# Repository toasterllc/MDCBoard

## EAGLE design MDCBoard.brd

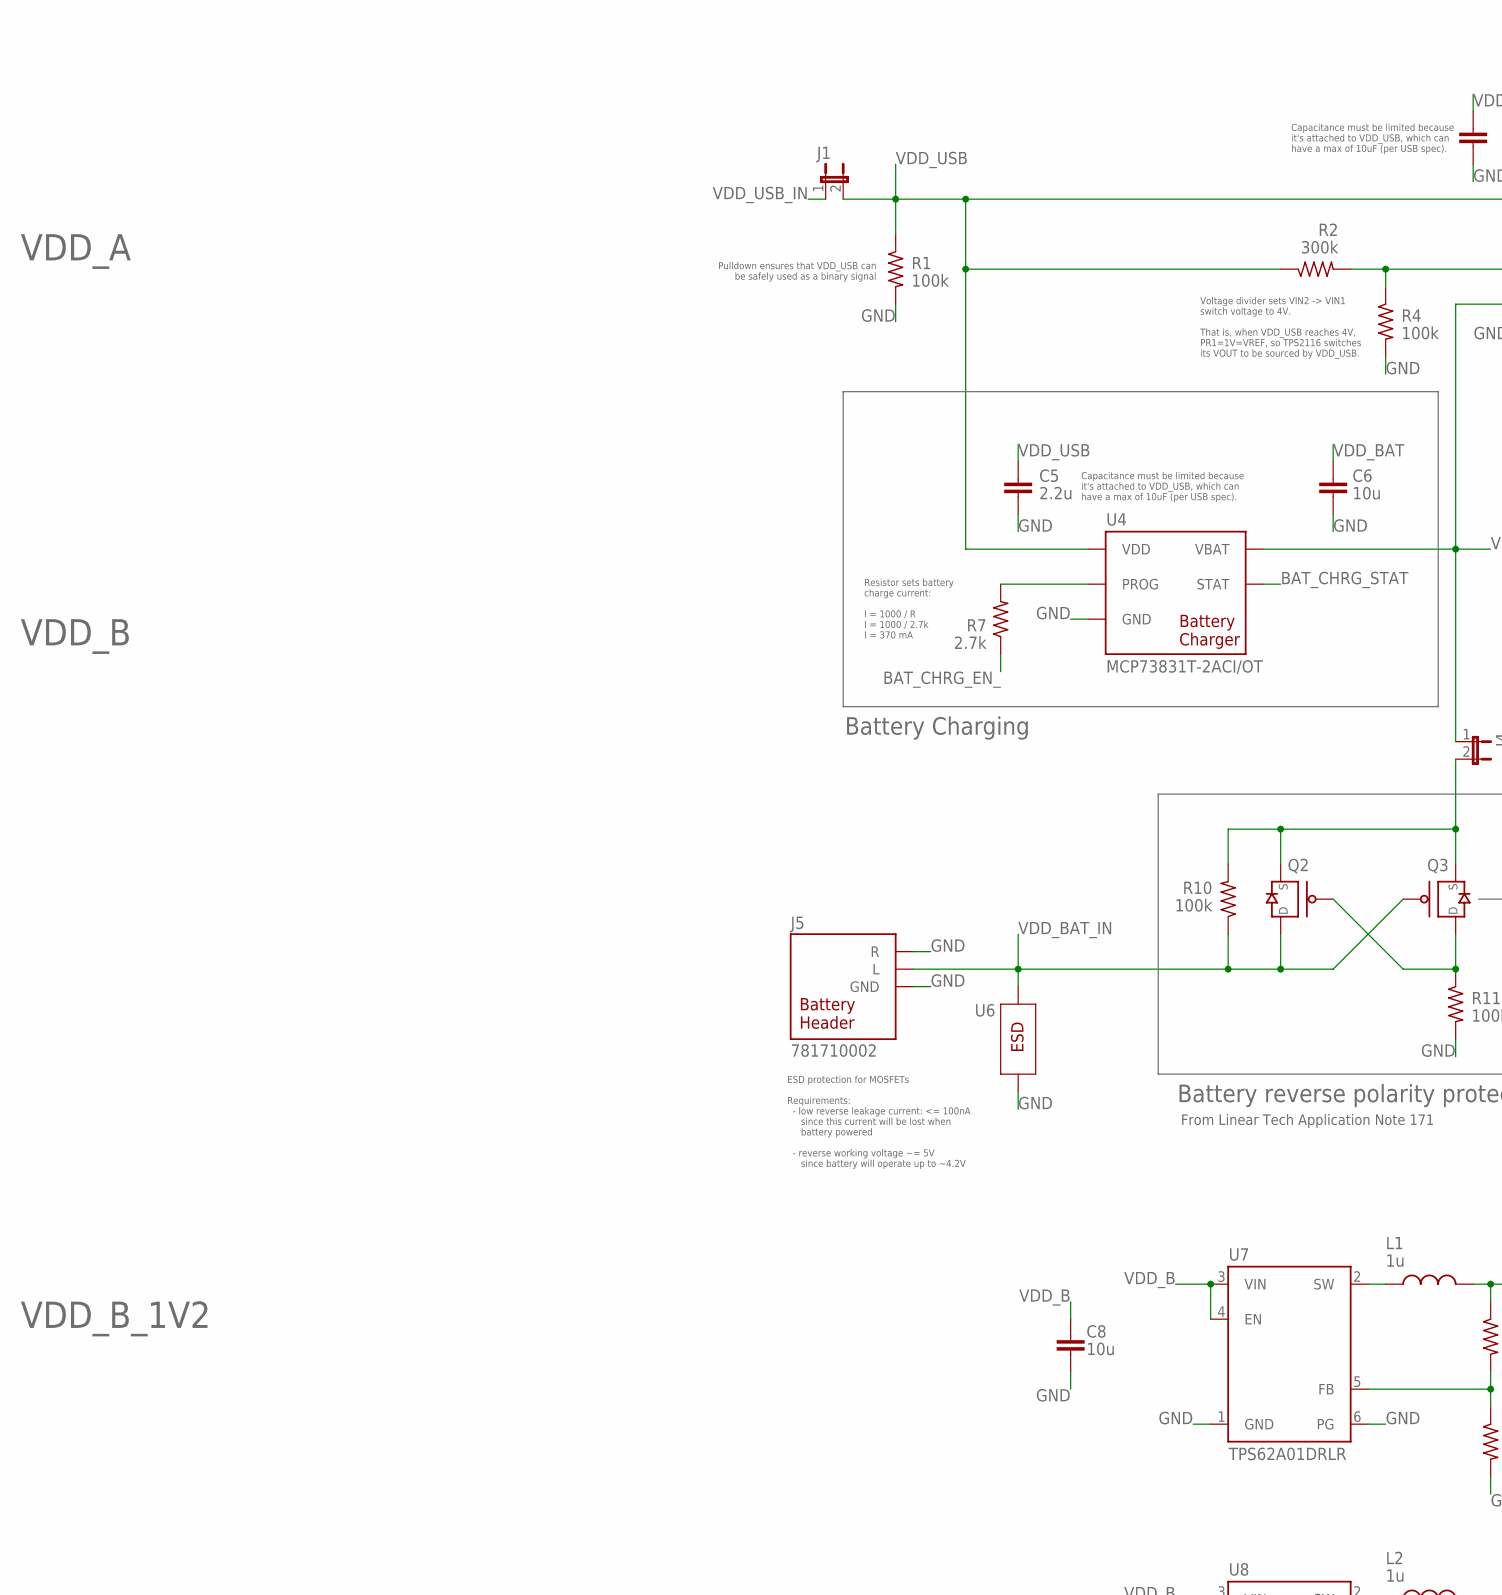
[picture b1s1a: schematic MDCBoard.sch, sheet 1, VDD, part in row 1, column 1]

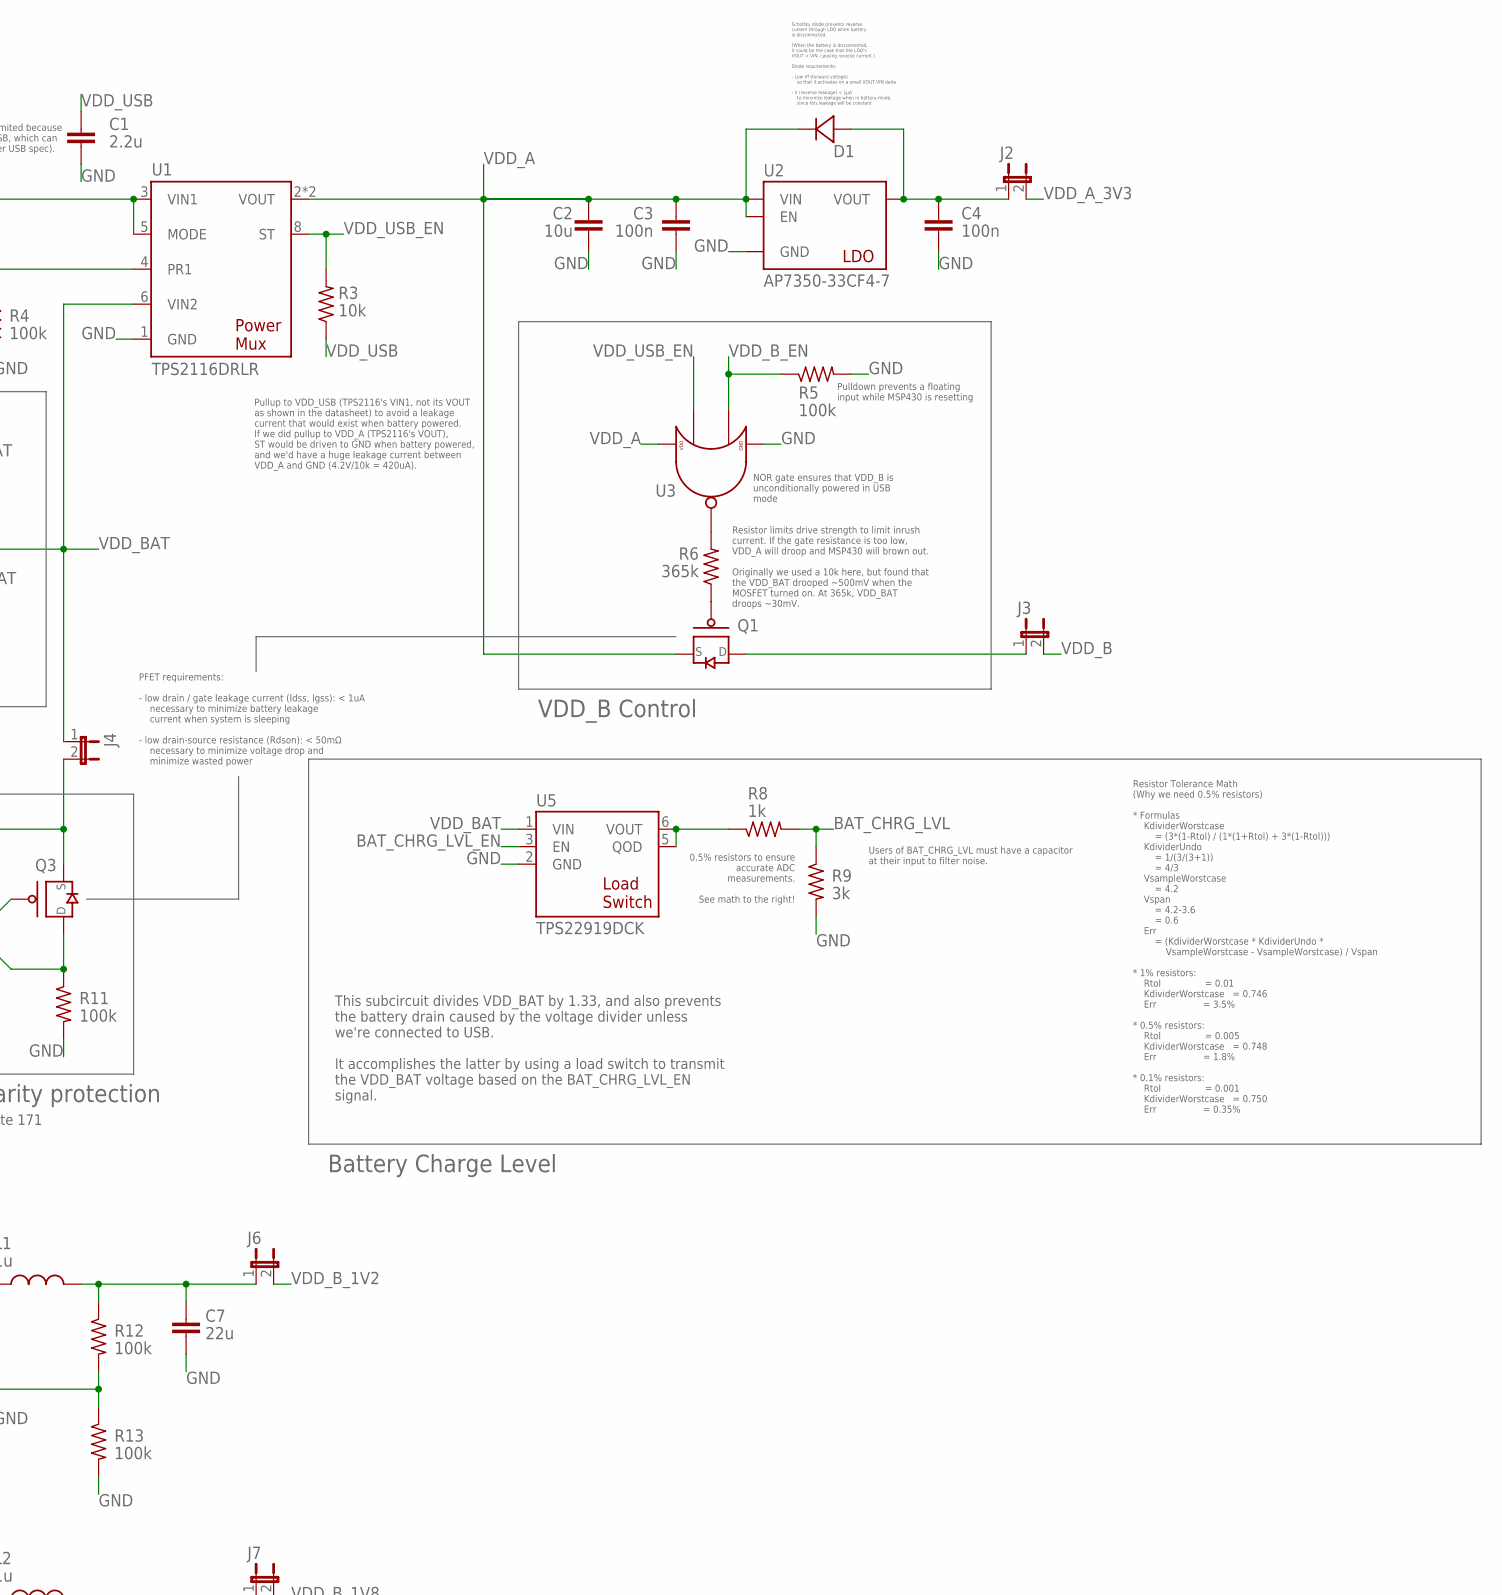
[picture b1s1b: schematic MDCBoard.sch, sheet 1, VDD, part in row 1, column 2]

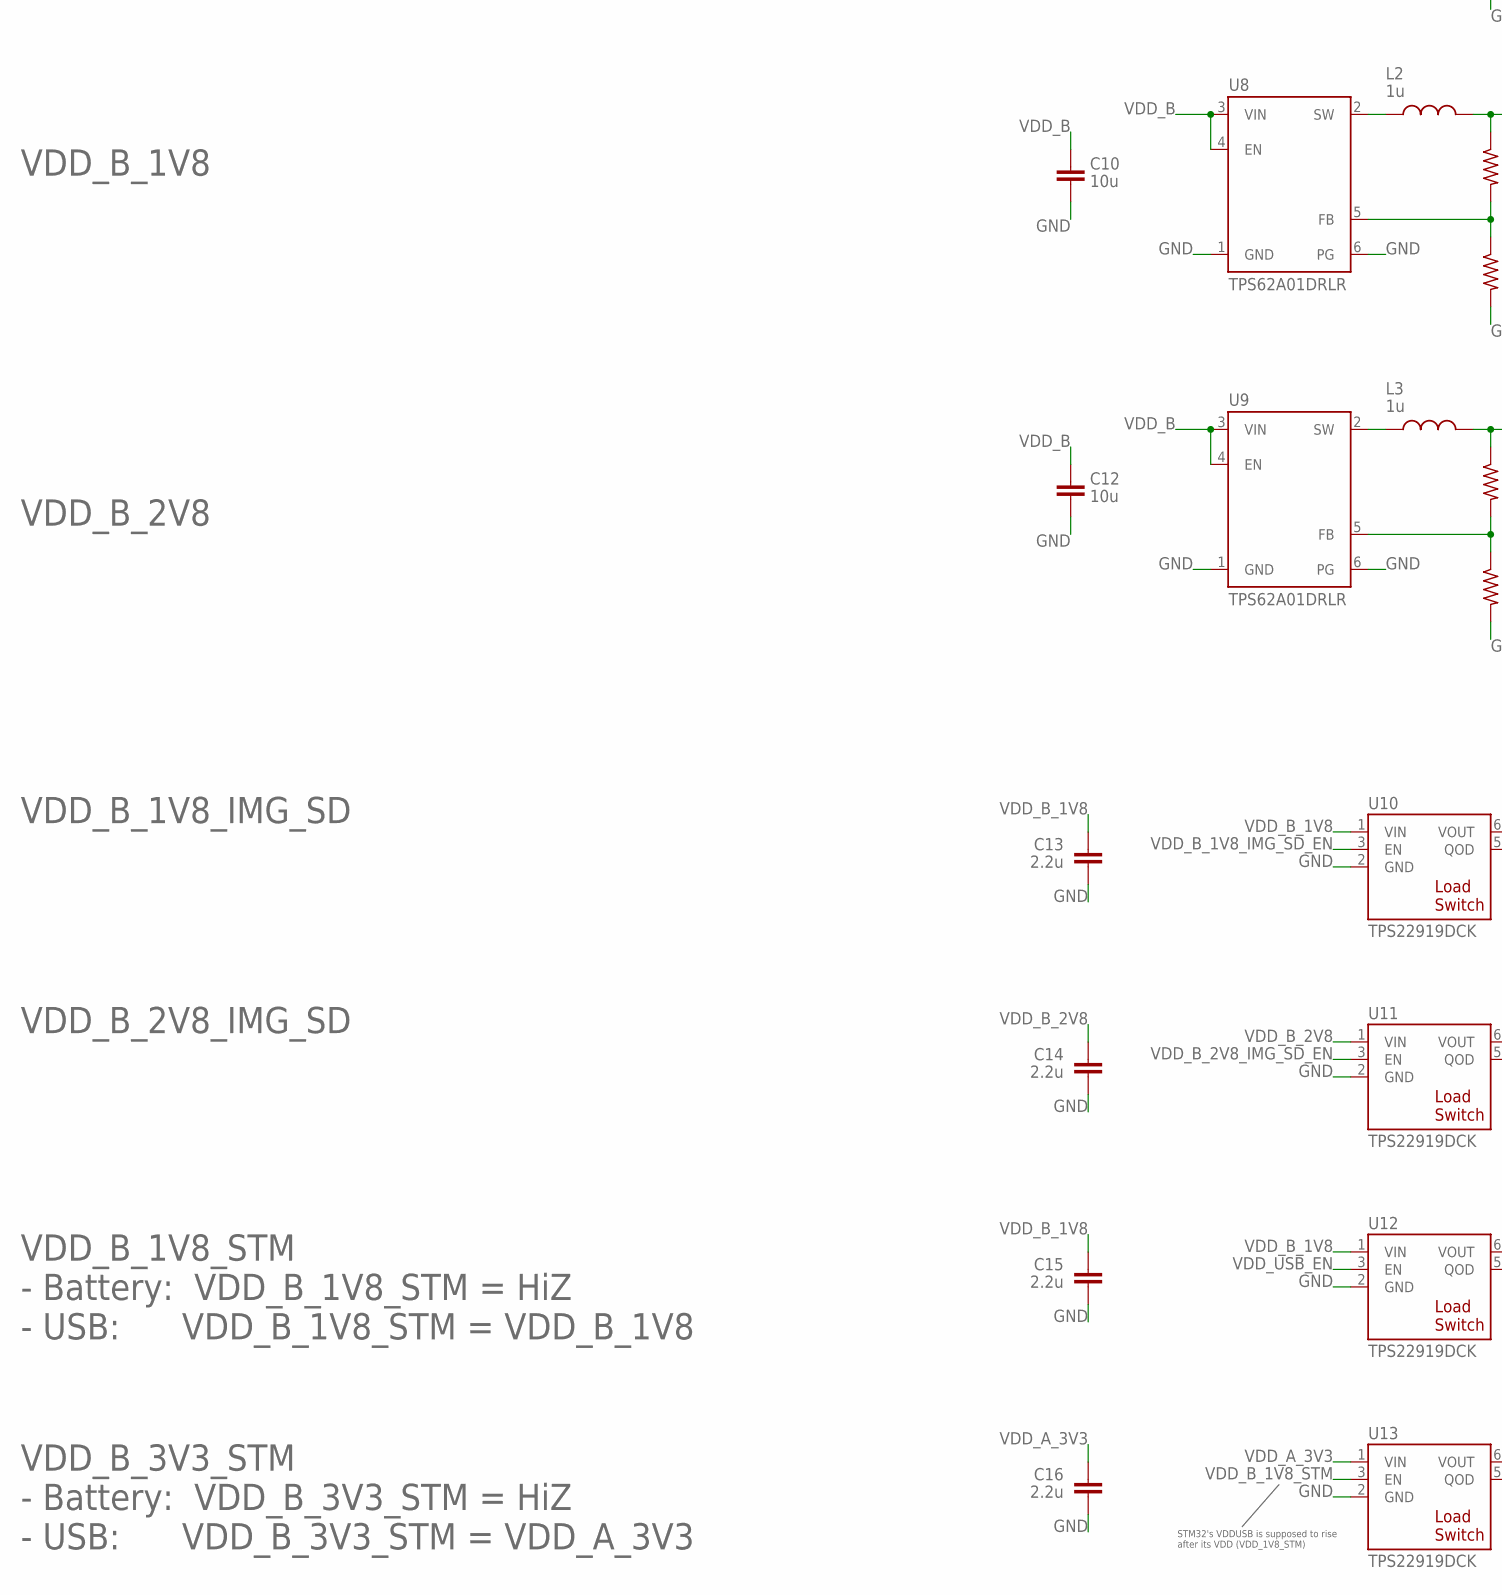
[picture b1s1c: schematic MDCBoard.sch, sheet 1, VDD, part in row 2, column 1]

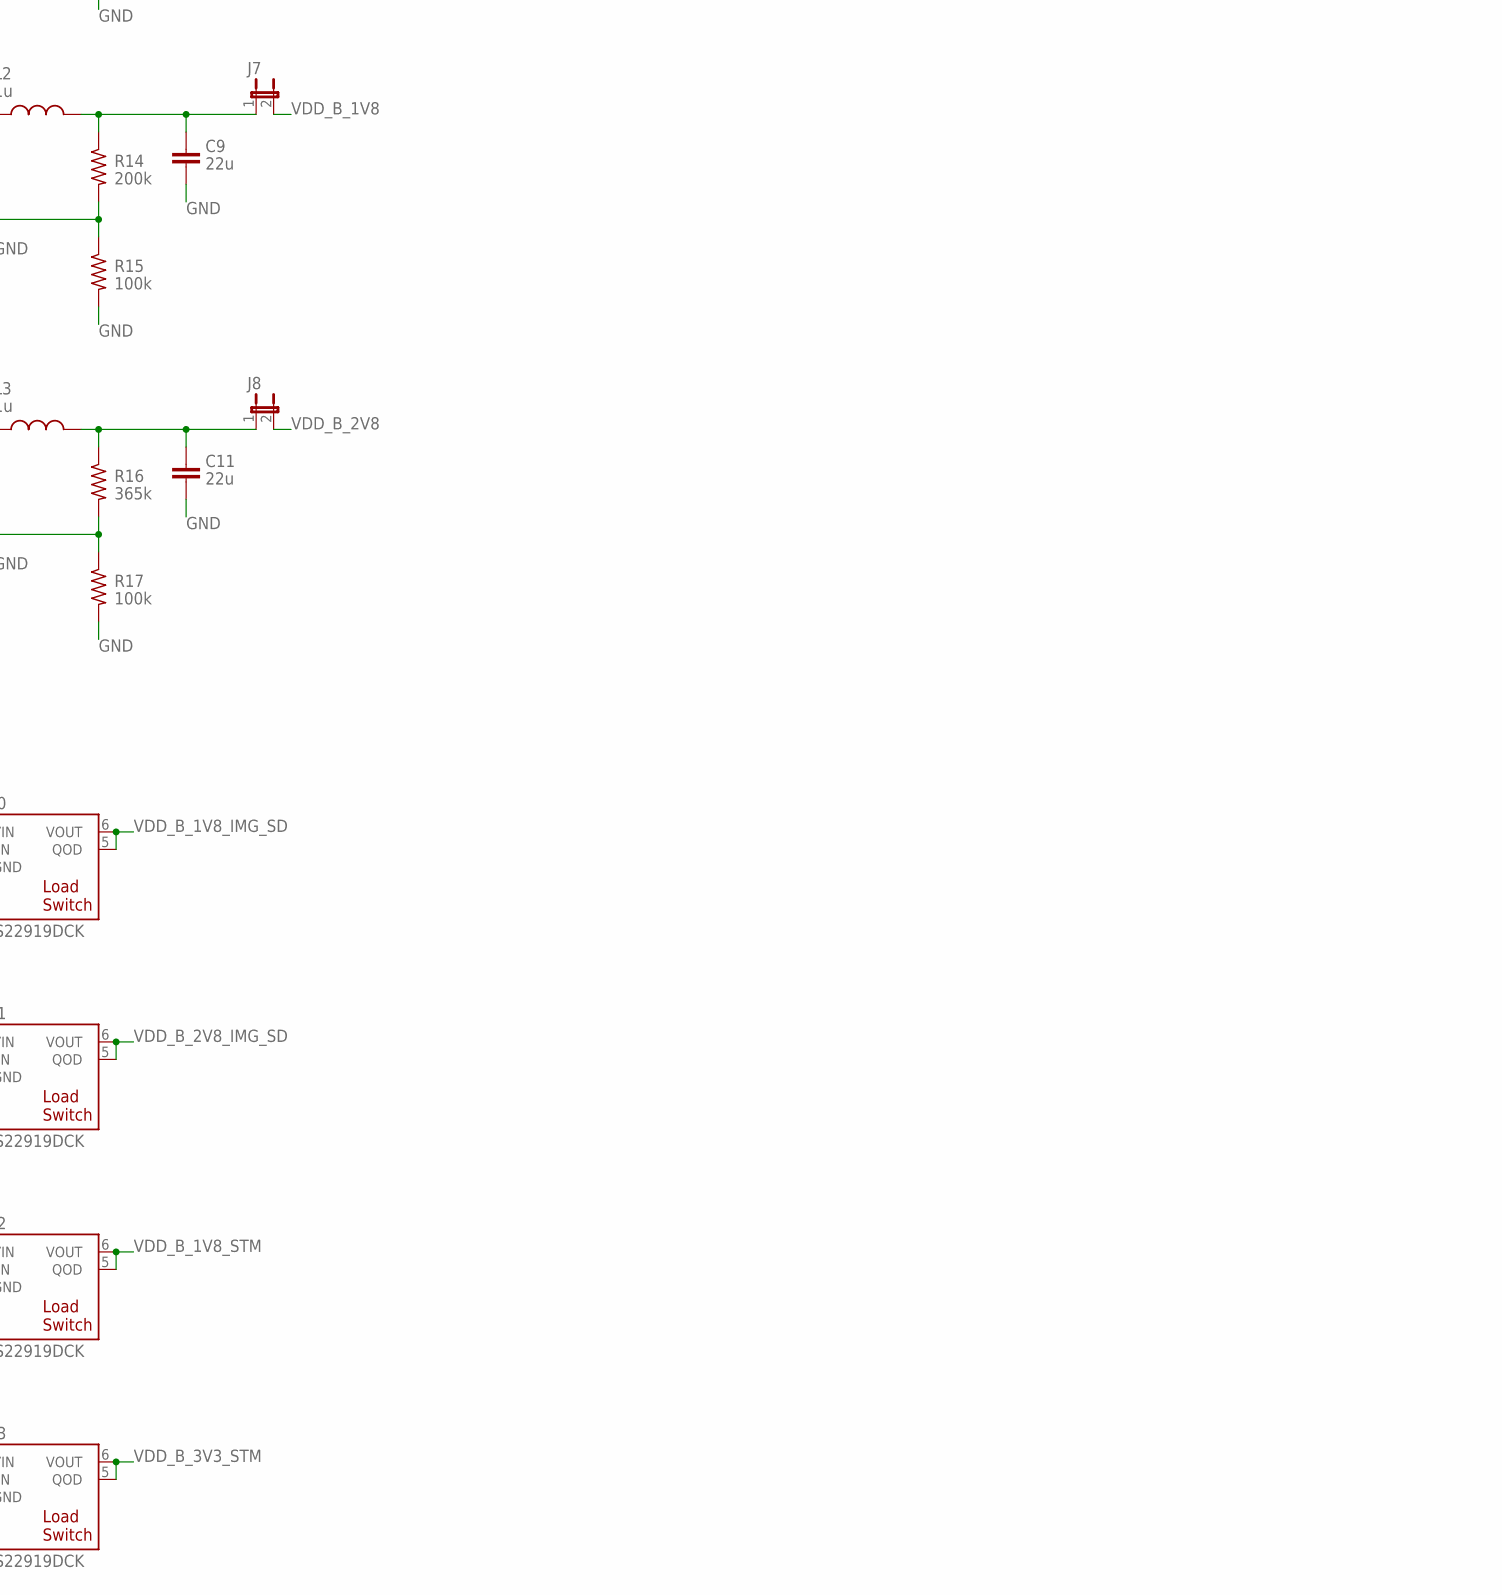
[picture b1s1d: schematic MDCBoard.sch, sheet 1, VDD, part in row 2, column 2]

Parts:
C1, C5, C13, C14, C15, C16: 2.2u; 0402
C2, C6, C8, C10, C12: 10u; 0805
C3, C4: 100n; 0402
C7, C9, C11: 22u; 0805
D1: ROHM-RB168MM-40; ROHM-SOD-123FL
J1, J2, J3, J4, J6, J7, J8: JUMPER-SOLDER-CLOSED
J5: BATTERY-HEADER-MOLEX-781710002; MOLEX-781710002
L1, L2, L3: 1u; 0806
Q1, Q2, Q3: PMOS-NEXPERIA-SOT1220; NEXPERIA-SOT1220
R1, R4, R5, R10, R11, R12, R13, R15, R17: 100k; 0402
R2: 300k; 0402
R3: 10k; 0402
R6, R16: 365k; 0402
R7: 2.7k; 0402
R8: 1k; 0402
R9: 3k; 0402
R14: 200k; 0402
U1: TI-TPS2116; TI-TPS2116DRLR
U2: DIODESINC-AP7350
U3: NEXPERIA-74LVC1G98-NOR; NEXPERIA-SOT363
U4: MICROCHIP-MCP7383X; MICROCHIP-MIC550X-SOT23-5
U5, U10, U11, U12, U13: TI-TPS22919DCK
U6: EATON-STN101
U7, U8, U9: TI-TPS62A01; TI-TPS62A01DRLR

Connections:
BAT_CHRG_EN_: R7.1; also elsewhere on the board
BAT_CHRG_LVL: R8.2, R9.1; also elsewhere on the board
BAT_CHRG_LVL_EN: U5.3 (EN); also elsewhere on the board
BAT_CHRG_STAT: U4.1 (STAT); also elsewhere on the board
GND: C1.2, C2.2, C3.2, C4.2, C5.2, C6.2, C7.2, C8.2, C9.2, C10.2, C11.2, C12.2, C13.2, C14.2, C15.2, C16.2, J5.2 (R), J5.3 (GND), J5.4 (GND), R1.2, R4.2, R5.2, R9.2, R11.2, R13.2, R15.2, R17.2, U1.1 (GND), U2.2 (GND), U3.2 (GND), U4.2 (GND), U5.2 (GND), U6.2, U7.1 (GND), U7.6 (PG), U8.1 (GND), U8.6 (PG), U9.1 (GND), U9.6 (PG), U10.2 (GND), U11.2 (GND), U12.2 (GND), U13.2 (GND); also elsewhere on the board
unnamed: J4.2, Q2.4 (S), Q2.8 (S), Q3.4 (S), Q3.8 (S), R10.2
unnamed: C4.1, D1.A, J2.1, U2.3 (VOUT)
unnamed: Q1.3 (G), R6.1
unnamed: R6.2, U3.4 (OUT)
unnamed: C11.1, J8.1, L3.2, R16.1
unnamed: L2.1, U8.2 (SW)
unnamed: R8.1, U5.5 (QOD), U5.6 (VOUT)
unnamed: R14.2, R15.1, U8.5 (FB)
unnamed: C9.1, J7.1, L2.2, R14.1
unnamed: R7.2, U4.5 (PROG)
unnamed: L3.1, U9.2 (SW)
unnamed: L1.1, U7.2 (SW)
unnamed: Q2.3 (G), Q3.1 (D), Q3.2 (D), Q3.5 (D), Q3.6 (D), Q3.7 (D), R11.1
unnamed: R16.2, R17.1, U9.5 (FB)
unnamed: R12.2, R13.1, U7.5 (FB)
unnamed: C7.1, J6.1, L1.2, R12.1
unnamed: R2.2, R4.1, U1.4 (PR1)
unnamed: J3.1, Q1.1 (D), Q1.2 (D), Q1.5 (D), Q1.6 (D), Q1.7 (D)
VDD_A: C2.1, C3.1, D1.C, Q1.4 (S), Q1.8 (S), U1.2 (VOUT), U1.7 (VOUT), U2.1 (EN), U2.4 (VIN), U3.3 (VDD), U3.5 (VDD)
VDD_A_3V3: C16.1, J2.2, U13.1 (VIN); also elsewhere on the board
VDD_B: C8.1, C10.1, C12.1, J3.2, U7.3 (VIN), U7.4 (EN), U8.3 (VIN), U8.4 (EN), U9.3 (VIN), U9.4 (EN)
VDD_BAT: C6.1, J4.1, U1.6 (VIN2), U4.3 (VBAT), U5.1 (VIN)
VDD_BAT_IN: J5.1 (L), Q2.1 (D), Q2.2 (D), Q2.5 (D), Q2.6 (D), Q2.7 (D), Q3.3 (G), R10.1, U6.1
VDD_B_1V2: J6.2; also elsewhere on the board
VDD_B_1V8: C13.1, C15.1, J7.2, U10.1 (VIN), U12.1 (VIN); also elsewhere on the board
VDD_B_1V8_IMG_SD: U10.5 (QOD), U10.6 (VOUT); also elsewhere on the board
VDD_B_1V8_IMG_SD_EN: U10.3 (EN); also elsewhere on the board
VDD_B_1V8_STM: U12.5 (QOD), U12.6 (VOUT), U13.3 (EN); also elsewhere on the board
VDD_B_2V8: C14.1, J8.2, U11.1 (VIN); also elsewhere on the board
VDD_B_2V8_IMG_SD: U11.5 (QOD), U11.6 (VOUT); also elsewhere on the board
VDD_B_2V8_IMG_SD_EN: U11.3 (EN); also elsewhere on the board
VDD_B_3V3_STM: U13.5 (QOD), U13.6 (VOUT); also elsewhere on the board
VDD_B_EN: R5.1, U3.6 (IN2); also elsewhere on the board
VDD_USB: C1.1, C5.1, J1.2, R1.1, R2.1, R3.1, U1.3 (VIN1), U1.5 (MODE), U4.4 (VDD)
VDD_USB_EN: R3.2, U1.8 (ST), U3.1 (IN1), U12.3 (EN)
VDD_USB_IN: J1.1; also elsewhere on the board

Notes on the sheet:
VDD_B_1V8_STM - Battery: VDD_B_1V8_STM = HiZ - USB: VDD_B_1V8_STM = VDD_B_1V8
VDD_A
VDD_B
VDD_B_1V2
VDD_B_1V8
VDD_B_2V8
VDD_B_1V8_IMG_SD
VDD_B_2V8_IMG_SD
VDD_B_3V3_STM - Battery: VDD_B_3V3_STM = HiZ - USB: VDD_B_3V3_STM = VDD_A_3V3
STM32's VDDUSB is supposed to rise after its VDD (VDD_1V8_STM)
NOR gate ensures that VDD_B is unconditionally powered in USB mode
VDD_B Control
Resistor limits drive strength to limit inrush current. If the gate resistance is too low, VDD_A will droop and MSP430 will brown out. Originally we used a 10k here, but found that the VDD_BAT drooped ~500mV when the MOSFET turned on. At 365k, VDD_BAT droops ~30mV.
From Linear Tech Application Note 171
Battery reverse polarity protection
Resistor sets battery charge current: I = 1000 / R I = 1000 / 2.7k I = 370 mA
Pulldown ensures that VDD_USB can be safely used as a binary signal
Schottky diode prevents reverse current through LDO when battery is disconnected. (When the battery is disconnected, it could be the case that the LDO's VOUT > VIN, causing reverse current.) Diode requirements: - Low Vf (forward voltage) so that it activates on a small VOUT-VIN delta - Ir (reverse 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
Voltage divider sets VIN2 -> VIN1 switch voltage to 4V. That is, when VDD_USB reaches 4V, PR1=1V=VREF, so TPS2116 switches its VOUT to be sourced by VDD_USB.
Capacitance must be limited because it's attached to VDD_USB, which can have a max of 10uF (per USB spec).
Battery Charge Level
Battery Charging
This subcircuit divides VDD_BAT by 1.33, and also prevents the battery drain caused by the voltage divider unless we're connected to USB. It accomplishes the latter by using a load switch to transmit the VDD_BAT voltage based on the BAT_CHRG_LVL_EN signal.
ESD protection for MOSFETs Requirements: - low reverse leakage current: <= 100nA since this current will be lost when battery powered - reverse working voltage ~= 5V since battery will operate up to ~4.2V
Users of BAT_CHRG_LVL must have a capacitor at their input to filter noise.
Pulldown prevents a floating input while MSP430 is resetting
PFET requirements: - low drain / gate leakage current (Idss, Igss): < 1uA necessary to minimize battery leakage current when system is sleeping - low drain-source resistance (Rdson): < 50mΩ necessary to minimize voltage drop and minimize wasted power
Resistor Tolerance Math (Why we need 0.5% resistors) * Formulas KdividerWorstcase = (3*(1-Rtol) / (1*(1+Rtol) + 3*(1-Rtol))) KdividerUndo = 1/(3/(3+1)) = 4/3 VsampleWorstcase = 4.2 Vspan = 4.2-3.6 = 0.6 Err = (KdividerWorstcase * KdividerUndo * VsampleWorstcase - VsampleWorstcase) / Vspan * 1% resi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
0.5% resistors to ensure accurate ADC measurements. See math to the right!
Pullup to VDD_USB (TPS2116's VIN1, not its VOUT as shown in the datasheet) to avoid a leakage current that would exist when battery powered. If we did pullup to VDD_A (TPS2116's VOUT), ST would be driven to GND when battery powered, and we'd have a huge leakage current between VDD_A and GND (4.2V/1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

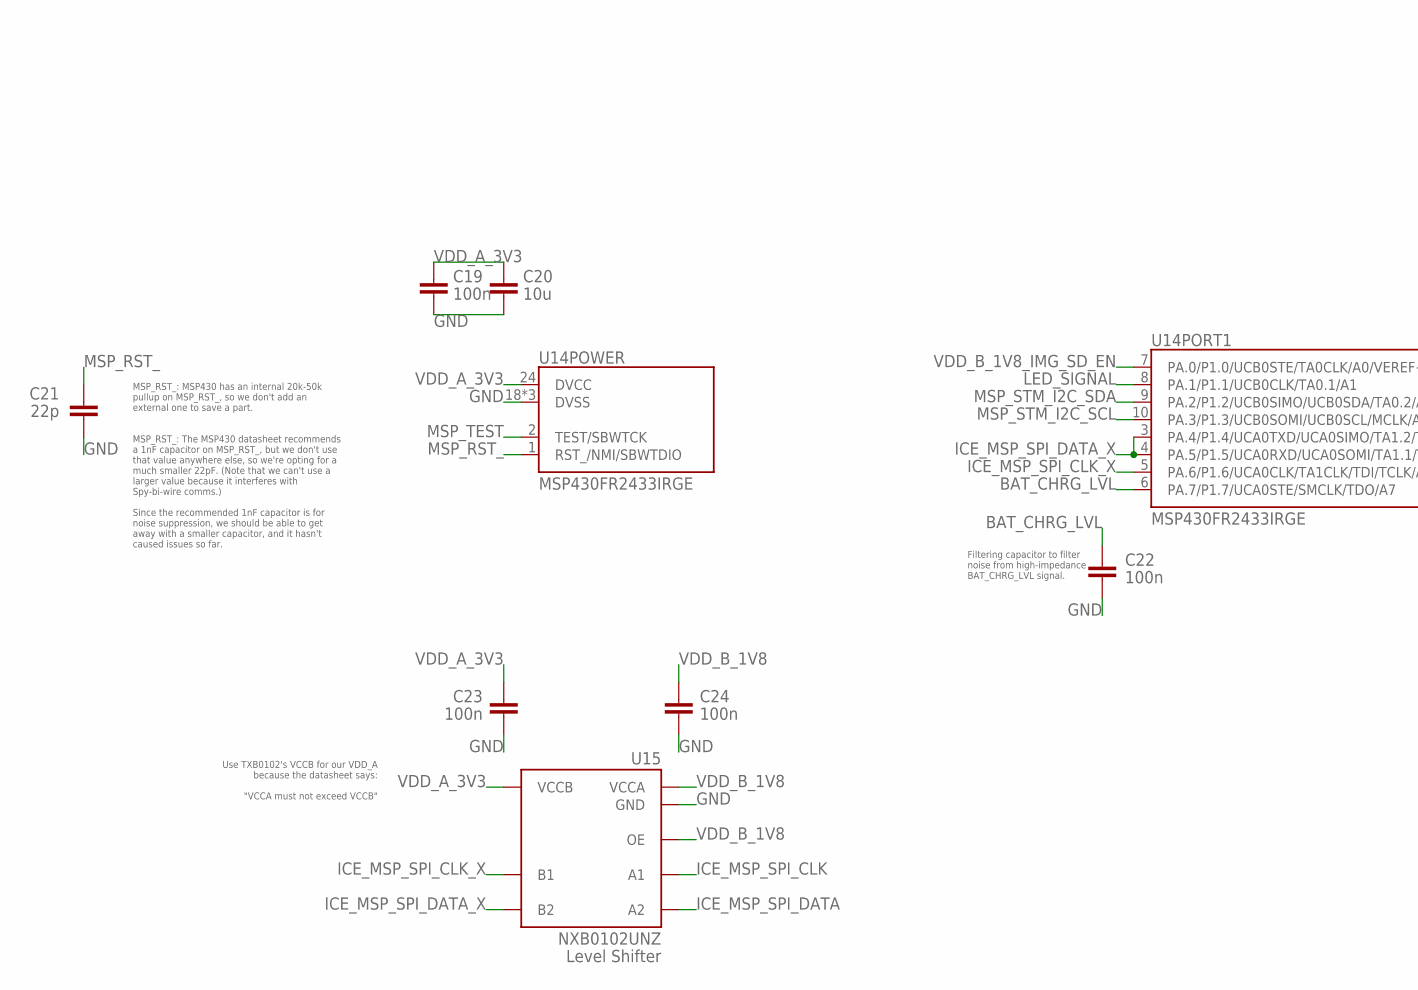
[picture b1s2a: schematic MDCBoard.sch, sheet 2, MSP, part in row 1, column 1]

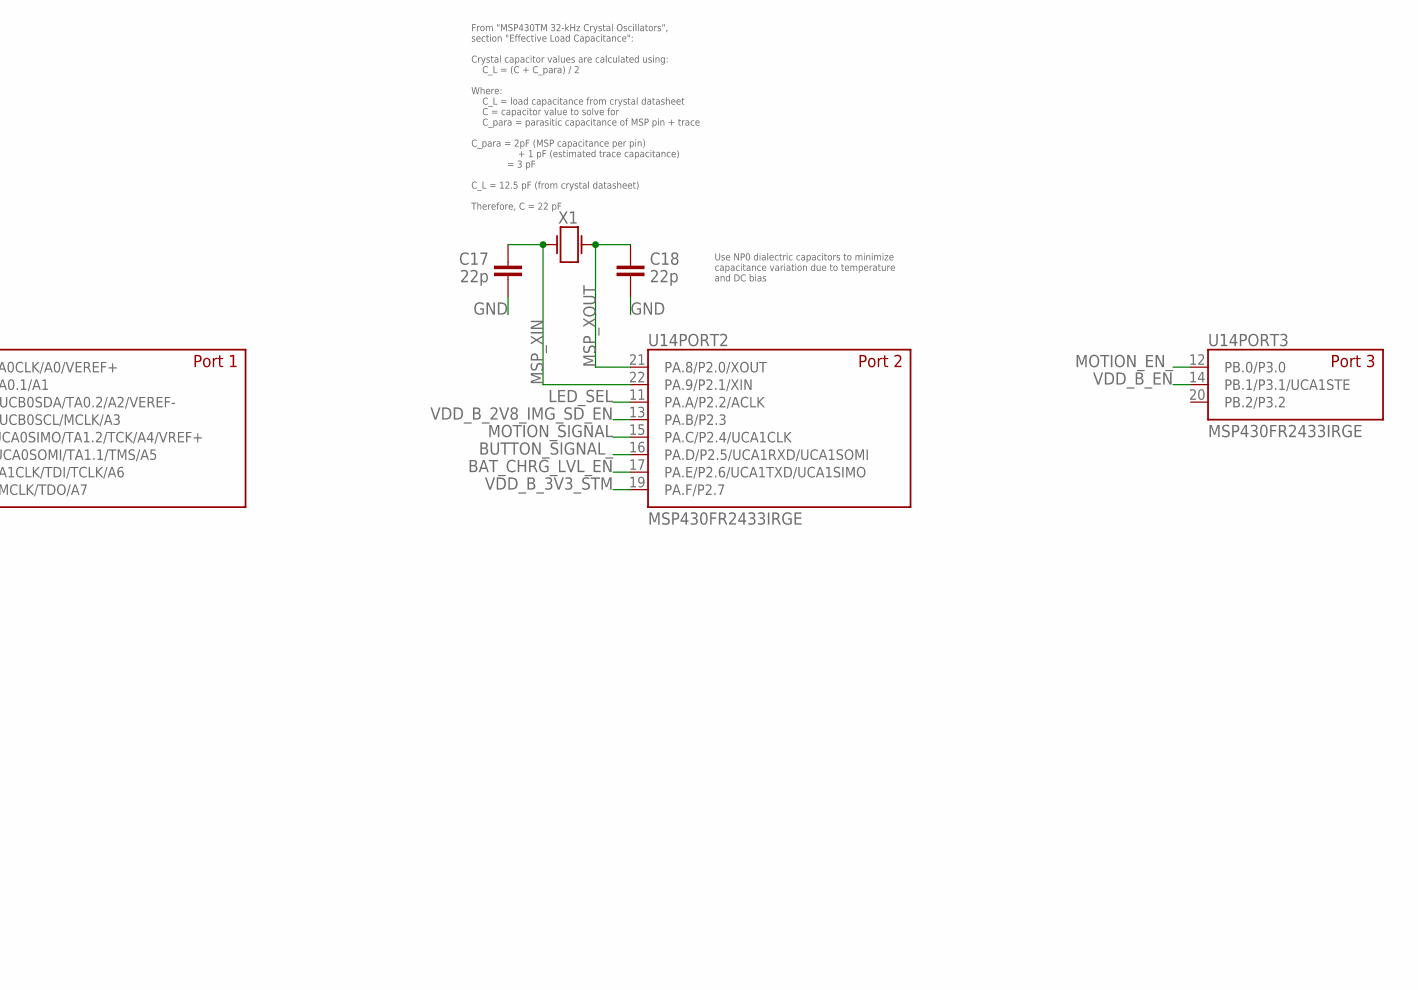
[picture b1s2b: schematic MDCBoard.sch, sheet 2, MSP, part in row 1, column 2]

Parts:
C17, C18, C21: 22p; 0402
C19, C22, C23, C24: 100n; 0402
C20: 10u; 0805
U14: TI-MSP430FR2433IRGE
U15: NEXPERIA-NXB0102; NEXPERIA-NXB0102UN
X1: EPSON-FC-135

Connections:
BAT_CHRG_LVL: C22.1, U14.6 (PA.7/P1.7/UCA0STE/SMCLK/TDO/A7); also elsewhere on the board
BAT_CHRG_LVL_EN: U14.17 (PA.E/P2.6/UCA1TXD/UCA1SIMO); also elsewhere on the board
BUTTON_SIGNAL_: U14.16 (PA.D/P2.5/UCA1RXD/UCA1SOMI); also elsewhere on the board
GND: C17.2, C18.2, C19.2, C20.2, C21.2, C22.2, C23.2, C24.2, U14.18 (DVSS), U14.23 (DVSS), U14.25 (DVSS), U15.B1 (GND); also elsewhere on the board
ICE_MSP_SPI_CLK: U15.D2 (A1); also elsewhere on the board
ICE_MSP_SPI_CLK_X: U14.5 (PA.6/P1.6/UCA0CLK/TA1CLK/TDI/TCLK/A6), U15.A2 (B1)
ICE_MSP_SPI_DATA: U15.D1 (A2); also elsewhere on the board
ICE_MSP_SPI_DATA_X: U14.3 (PA.4/P1.4/UCA0TXD/UCA0SIMO/TA1.2/TCK/A4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), U14.4 (PA.5/P1.5/UCA0RXD/UCA0SOMI/TA1.1/TMS/A5), U15.A1 (B2)
LED_SEL: U14.11 (PA.A/P2.2/ACLK); also elsewhere on the board
LED_SIGNAL: U14.8 (PA.1/P1.1/UCB0CLK/TA0.1/A1); also elsewhere on the board
MOTION_EN_: U14.12 (PB.0/P3.0); also elsewhere on the board
MOTION_SIGNAL: U14.15 (PA.C/P2.4/UCA1CLK); also elsewhere on the board
MSP_RST_: C21.1, U14.1 (RST_/NMI/SBWTDIO); also elsewhere on the board
MSP_STM_I2C_SCL: U14.10 (PA.3/P1.3/UCB0SOMI/UCB0SCL/MCLK/A3); also elsewhere on the board
MSP_STM_I2C_SDA: U14.9 (PA.2/P1.2/UCB0SIMO/UCB0SDA/TA0.2/A2/VER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); also elsewhere on the board
MSP_TEST: U14.2 (TEST/SBWTCK); also elsewhere on the board
MSP_XIN: C17.1, U14.22 (PA.9/P2.1/XIN), X1.2 (B)
MSP_XOUT: C18.1, U14.21 (PA.8/P2.0/XOUT), X1.1 (A)
VDD_A_3V3: C19.1, C20.1, C23.1, U14.24 (DVCC), U15.B2 (VCCB); also elsewhere on the board
VDD_B_1V8: C24.1, U15.C1 (VCCA), U15.C2 (OE); also elsewhere on the board
VDD_B_1V8_IMG_SD_EN: U14.7 (PA.0/P1.0/UCB0STE/TA0CLK/A0/VEREF+); also elsewhere on the board
VDD_B_2V8_IMG_SD_EN: U14.13 (PA.B/P2.3); also elsewhere on the board
VDD_B_3V3_STM: U14.19 (PA.F/P2.7); also elsewhere on the board
VDD_B_EN: U14.14 (PB.1/P3.1/UCA1STE); also elsewhere on the board

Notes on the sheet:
From "MSP430TM 32-kHz Crystal Oscillators", section "Effective Load Capacitance": Crystal capacitor values are calculated using: C_L = (C + C_para) / 2 Where: C_L = load capacitance from crystal datasheet C = capacitor value to solve for C_para = parasitic capacitance of MSP pin + trace C_para = 2p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
Use NP0 dialectric capacitors to minimize capacitance variation due to temperature and DC bias
MSP_RST_: MSP430 has an internal 20k-50k pullup on MSP_RST_, so we don't add an external one to save a part.
MSP_RST_: The MSP430 datasheet recommends a 1nF capacitor on MSP_RST_, but we don't use that value anywhere else, so we're opting for a much smaller 22pF. (Note that we can't use a larger value because it interferes with Spy-bi-wire comms.) Since the recommended 1nF capacitor is for noise suppressi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
Use TXB0102's VCCB for our VDD_A because the datasheet says: "VCCA must not exceed VCCB"
Filtering capacitor to filter noise from high-impedance BAT_CHRG_LVL signal.

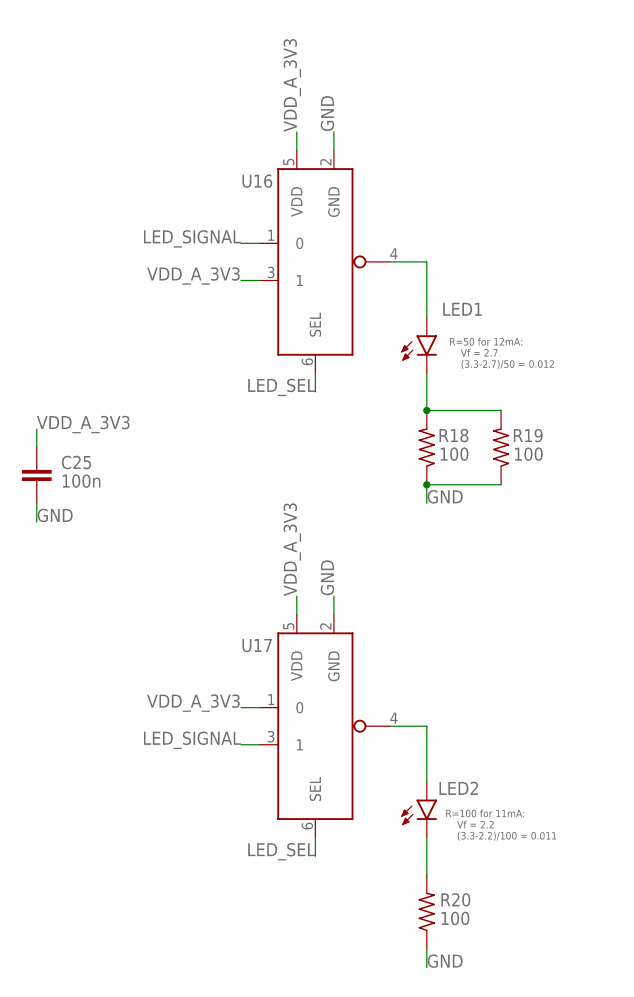
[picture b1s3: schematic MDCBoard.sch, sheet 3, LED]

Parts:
C25: 100n; 0402
LED1, LED2: LEDOSRAM-TOPLED-E1608; OSRAM-TOPLED-E1608
R18, R19, R20: 100; 0402
U16, U17: NEXPERIA-74LVC1G98-MUX-INV-OUTPUT; NEXPERIA-SOT363

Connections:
GND: C25.2, R18.1, R19.1, R20.1, U16.2 (GND), U17.2 (GND); also elsewhere on the board
LED_SEL: U16.6 (SEL), U17.6 (SEL); also elsewhere on the board
LED_SIGNAL: U16.1 (0), U17.3 (1); also elsewhere on the board
unnamed: LED1.A, U16.4 (OUT)
unnamed: LED2.A, U17.4 (OUT)
unnamed: LED2.C, R20.2
unnamed: LED1.C, R18.2, R19.2
VDD_A_3V3: C25.1, U16.3 (1), U16.5 (VDD), U17.1 (0), U17.5 (VDD); also elsewhere on the board

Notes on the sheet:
R=100 for 11mA: Vf = 2.2 (3.3-2.2)/100 = 0.011
R=50 for 12mA: Vf = 2.7 (3.3-2.7)/50 = 0.012

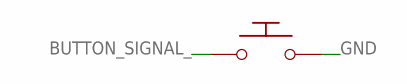
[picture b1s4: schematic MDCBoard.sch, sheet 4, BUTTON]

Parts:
SW1: TACTILE-SWITCH; DEALON-TD-1624UR-180

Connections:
BUTTON_SIGNAL_: SW1.1; also elsewhere on the board
GND: SW1.2; also elsewhere on the board

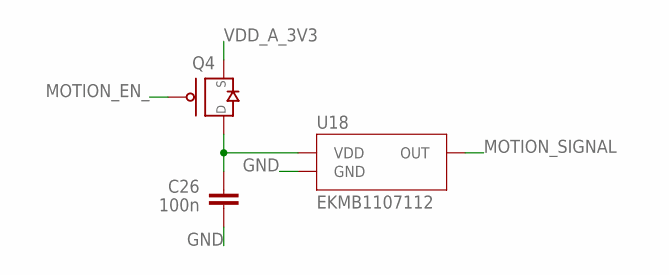
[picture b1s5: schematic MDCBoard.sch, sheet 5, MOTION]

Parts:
C26: 100n; 0402
Q4: DIODESINC-DMG2305UX
U18: PANASONIC-EKMB110711X

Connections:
GND: C26.2, U18.3 (GND); also elsewhere on the board
MOTION_EN_: Q4.G; also elsewhere on the board
MOTION_SIGNAL: U18.2 (OUT); also elsewhere on the board
unnamed: C26.1, Q4.D, U18.1 (VDD)
VDD_A_3V3: Q4.S; also elsewhere on the board
